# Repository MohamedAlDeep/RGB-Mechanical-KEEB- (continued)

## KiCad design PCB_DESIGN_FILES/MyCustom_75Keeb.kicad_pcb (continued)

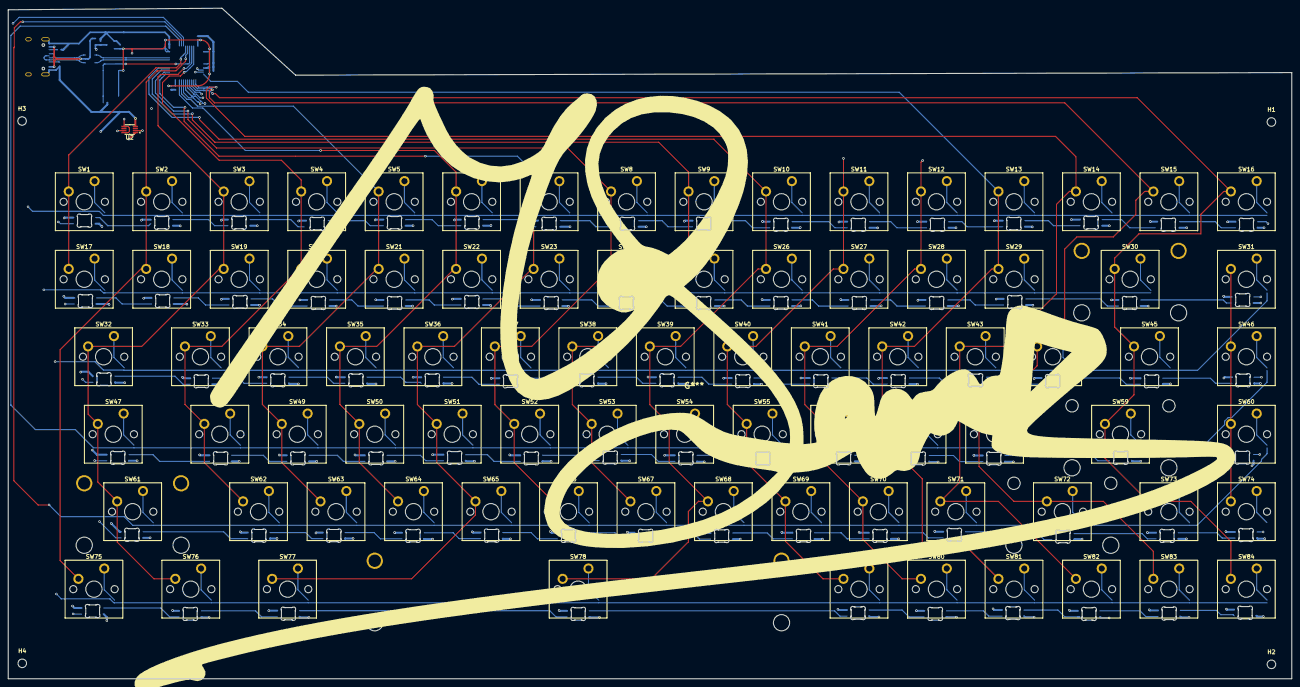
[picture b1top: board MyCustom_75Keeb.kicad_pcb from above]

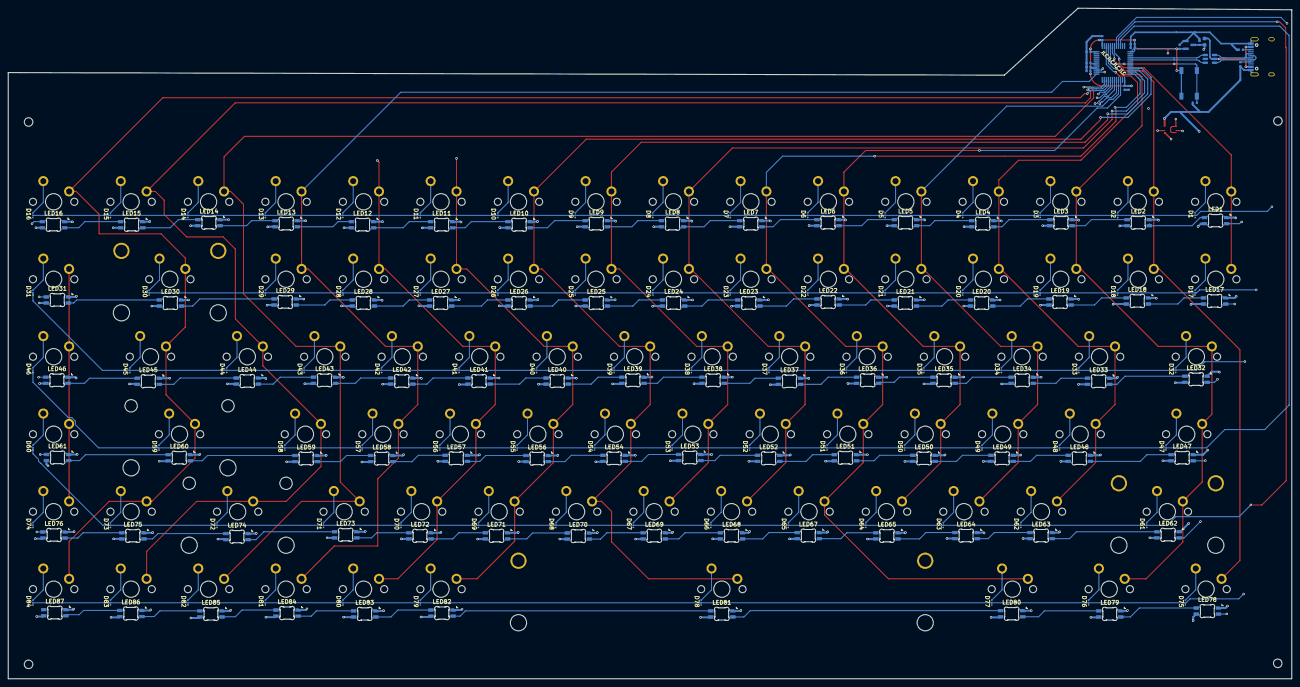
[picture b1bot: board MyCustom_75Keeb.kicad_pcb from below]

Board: 4 copper layers, 315.6 x 164.9 mm, 282 parts (188 on the bottom side), 203 nets.

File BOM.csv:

Id,Designator,Footprint PCB ONLY,Quantity,Designation,Supplier (LINK),Price,,Total
,,,,,,,,
,,,,,,,,
,,,,,,,,
,,,,,,,,
,"Redragon A101 Replacement Keycaps,104 Keyboard Keycaps, Compatible, Mechanical Keyboard Keycaps Inclusive Keypuller for Mechanical Keyboard || White",,1,,https://www.amazon.eg/-/en/Redragon-Replacement-Compatible-M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,12.63,,12.63
6,GATERON G Pro 3.0 Switches Pre-lubed 5 pinS RGB Linear for Gaming Mechanical Keyboard (Yellow),,1,,https://www.amazon.eg/-/en/GATERON-Switches-Pre-lubed-Mechan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,10.52,,10.52
7,U2,VSSOP-8_2.3x2mm_P0.5mm,1,74LVCH2T45DC,https://jlcpcb.com/partdetail/Nexperia-74LVCH2T45DC125/C548924,0.564,,0.564
8,"LED81,LED30,LED64,LED1,LED58,LED17,LED39,LED36,LED47,LED24,LED80,LED20,LED31,LED68,LED23,LED7,LED63,LED2,LED70,LED26,LED73,LED5,LED67,LED3,LED85,LED25,LED62,LED18,LED69,LED41,LED13,LED9,LED46,LED48,LED53,LED86,LED38,LED42,LED44,LED14,LED71,LED83,LED11,LED12,LED15,LED76,LED72,LED84,LED32,LED29,LED37,LED51,LED59,LED79,LED28,LED56,LED8,LED19,LED65,LED35,LED57,LED10,LED60,LED43,LED34,LED61,LED27,LED16,LED87,LED50,LED45,LED54,LED40,LED22,LED4,LED6,LED82,LED74,LED78,LED21,LED49,LED75,LED33,LED52",LED_6028R,84,SK6812MINI-E,https://jlcpcb.com/partdetail/OPSCOOptoelectronics-SK6812MIN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,0.0578,,4.8552
9,"D77,D49,D82,D24,D37,D76,D83,D3,D81,D58,D72,D56,D40,D10,D45,D53,D20,D16,D28,D70,D1,D52,D38,D19,D11,D41,D50,D34,D9,D64,D22,D23,D47,D12,D43,D80,D2,D14,D17,D67,D7,D5,D71,D42,D78,D73,D68,D57,D33,D4,D65,D69,D13,D66,D27,D36,D74,D32,D15,D6,D84,D31,D8,D18,D61,D39,D46,D48,D30,D55,D35,D62,D60,D51,D59,D29,D25,D63,D21,D26,D44,D79,D75,D54",D_0201_0603Metric,84,D,https://jlcpcb.com/partdetail/Comchip-CZRU52C2V7HF/C2886070,0.06,,5.04
10,"R7,R6",Resistor_0402,2,5.1k,https://jlcpcb.com/partdetail/26487-0402WGF1002TCE/C25744,0.0006,,0.0012
11,"C10,C7,C3,C1,C2",Capacitor_0402,5,100nF,https://jlcpcb.com/partdetail/1877-CL05B104KO5NNNC/C1525,0.0012,,0.006
12,J1,USB_C_HRO_TYPE-C-31-M-12,1,USB_C,https://jlcpcb.com/partdetail/Korean_HropartsElec-TYPE_C_31_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,0.17,,0.17
13,U3,ESD_SOT-23-6,1,USBLC6-2SC6,https://jlcpcb.com/partdetail/2790619-USBLC62SC6/C2687116,0.0368,,0.0368
14,C8,Capacitor_0402,1,10nF,https://jlcpcb.com/partdetail/53938-CL05A105KA5NQNC/C52923,0.0029,,0.0029
15,U1,Package_LQFP-48_7x7mm_P0.5,1,STM32F072CBT6,https://jlcpcb.com/partdetail/STMicroelectronics-STM32F072CB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,1.3005,,1.3005
16,"C12,C9,C13",Capacitor_0402,3,1uF,https://jlcpcb.com/partdetail/15869-CL05B103KB5NNNC/C15195,0.0014,,0.0042
17,"C11,C6",Capacitor_0402,2,4.7uF,https://jlcpcb.com/partdetail/24469-CL05A475MP5NRNC/C23733,0.0046,,0.0092
18,U4,Voltage_SOT-23,1,XC6206,https://jlcpcb.com/partdetail/TorexSemicon-XC6206P332MRG/C5446,0.0998,,0.0998
19,R5,Resistor_0402,1,10k,https://jlcpcb.com/partdetail/26648-0402WGF5101TCE/C25905,0.0005,,0.0005
20,F1,Fuse_0603,1,500mA,https://jlcpcb.com/partdetail/Hongda-2009T500mA250V/C529783,0.0551,,0.0551
21,SW343,Button_TL3342,1,SW_Push,https://jlcpcb.com/partdetail/Alpsalpine-SKQGABE010/C115351,0.0005,,0.0005
,,,,,,,,
,,,,,,,,
TOTAL IN USD,,,,,,,,12.1459
PCB 5 pics,,,,,,,,50
,,,,,,,,75

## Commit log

2025-12-04 all files
2025-12-04 all files after edit
2025-12-04 Readme correction
2025-12-04 readme fix
2025-12-04 image
2025-12-07 BOM fix
2025-12-07 organized
2025-12-13 firmware
2025-12-28 aliexpress
2025-12-28 aliexpress 2
2026-01-06 Update BOM.csv to reflect new total labels
2026-01-16 PCB CASE step files
2026-01-16 PCB Case Design Images
2026-01-16 Document keyboard case design and end result
    Added details about the keyboard case design and images.
2026-01-16 Finalizing
